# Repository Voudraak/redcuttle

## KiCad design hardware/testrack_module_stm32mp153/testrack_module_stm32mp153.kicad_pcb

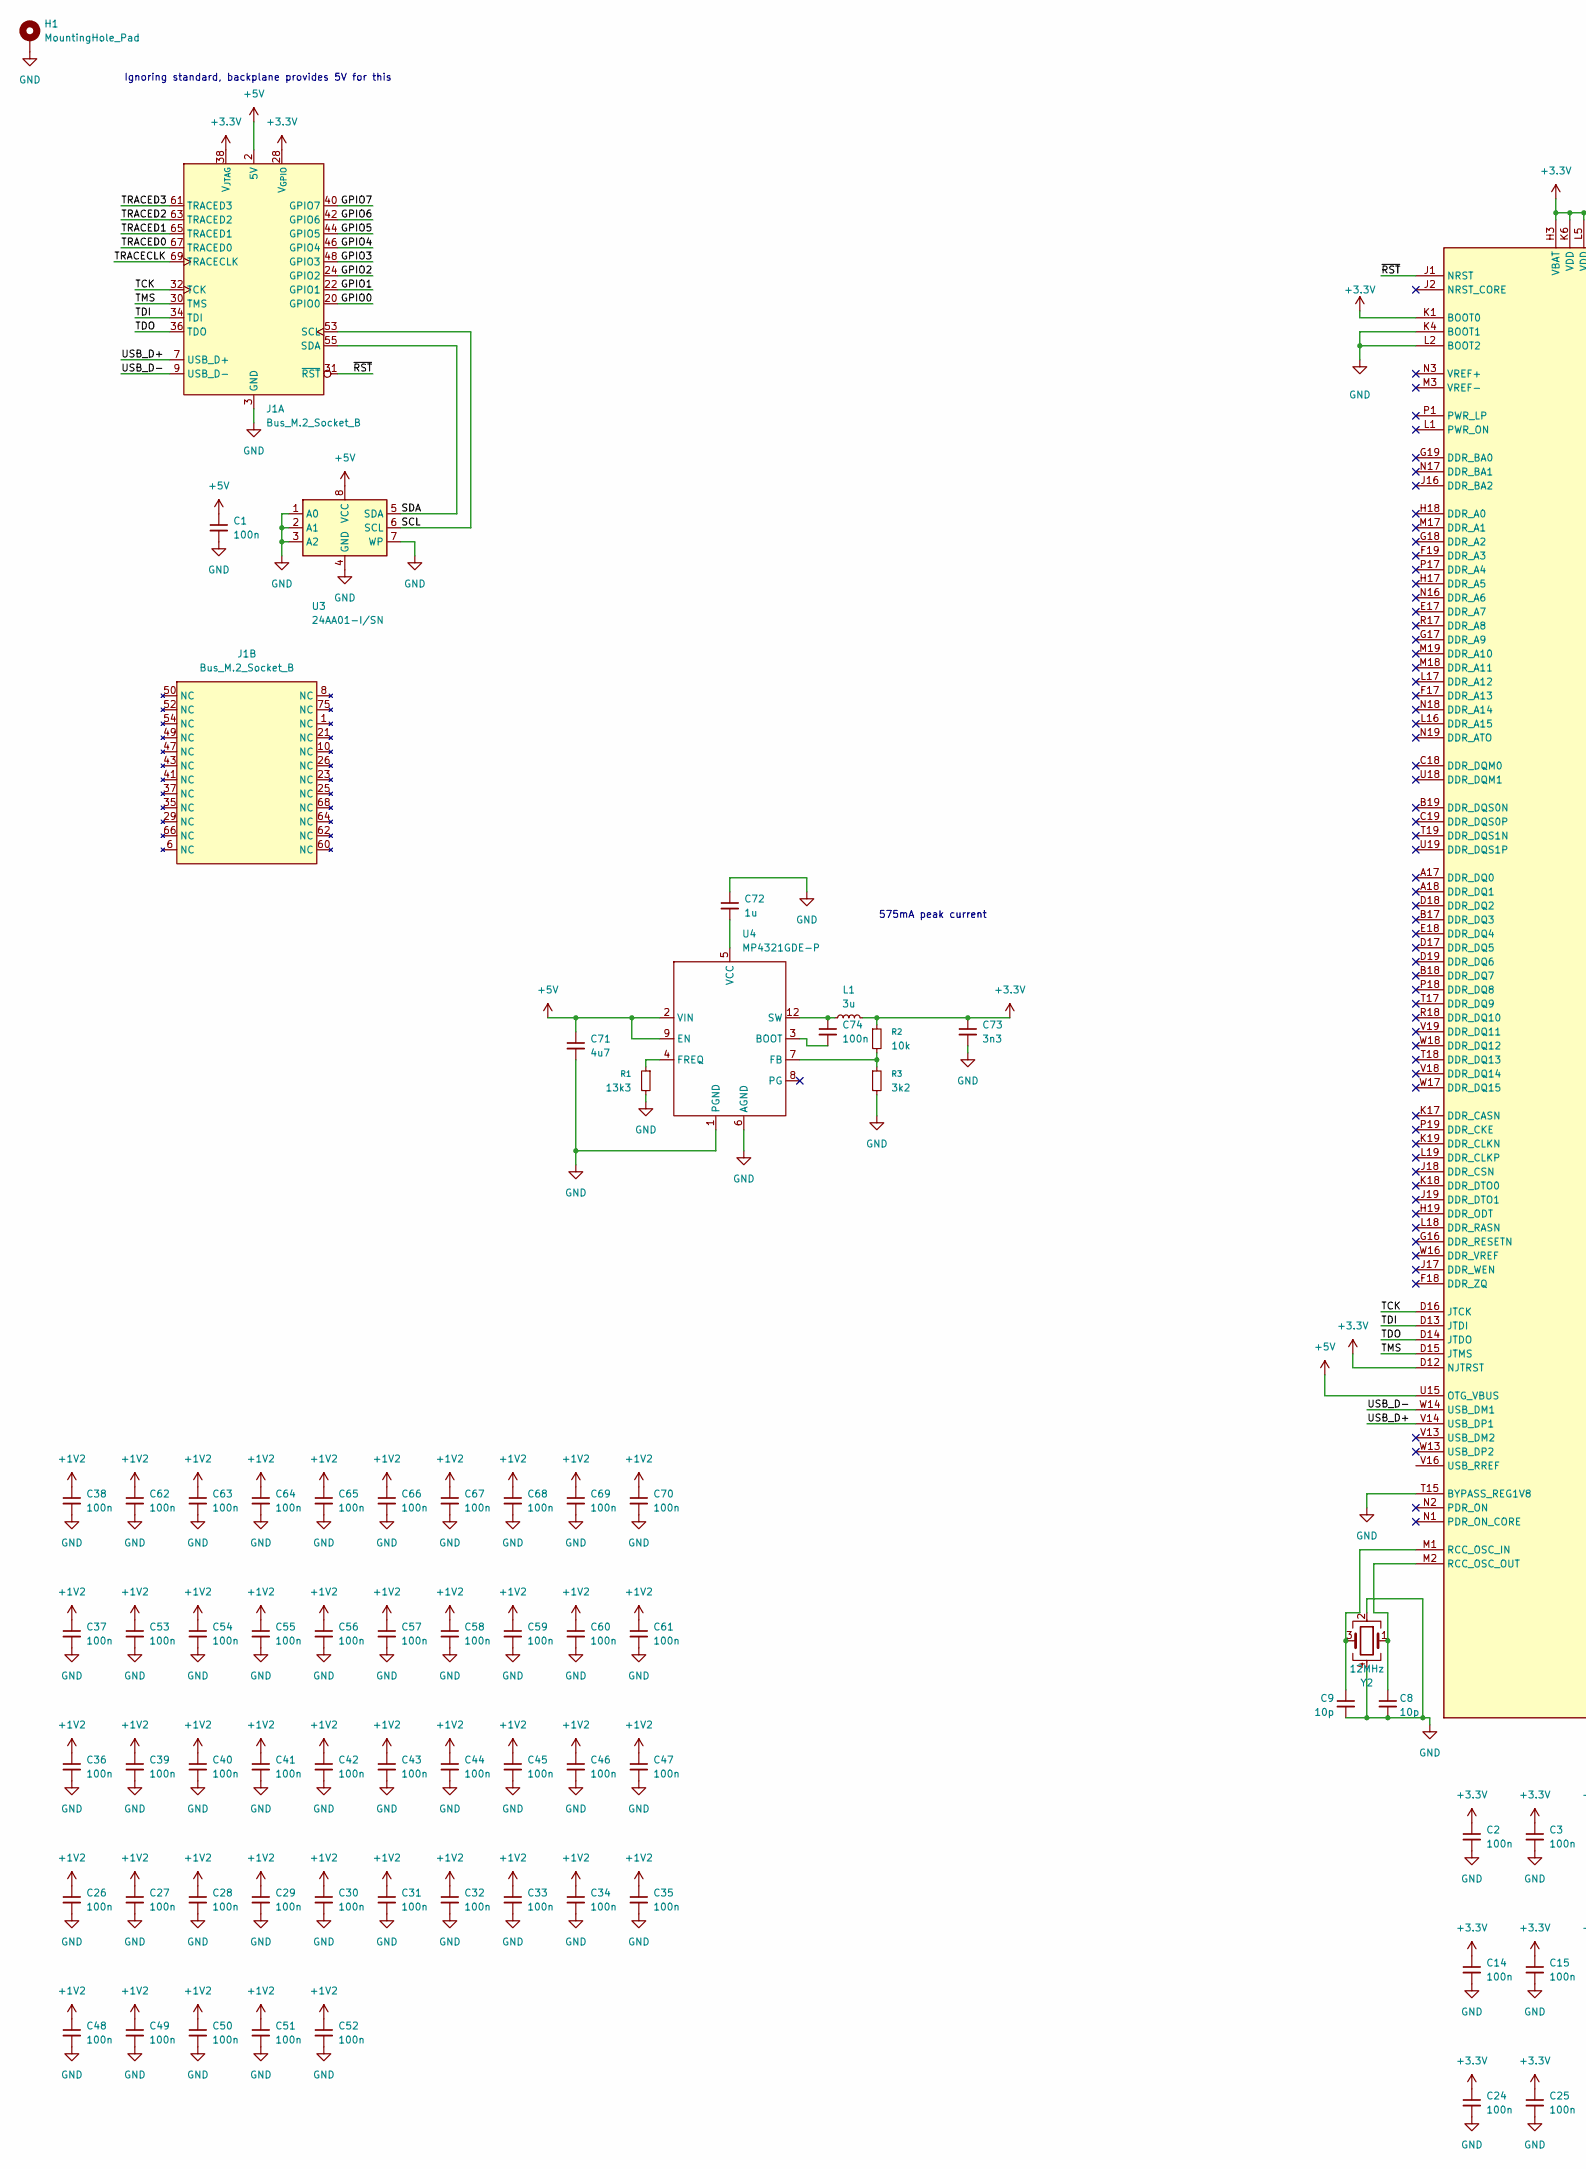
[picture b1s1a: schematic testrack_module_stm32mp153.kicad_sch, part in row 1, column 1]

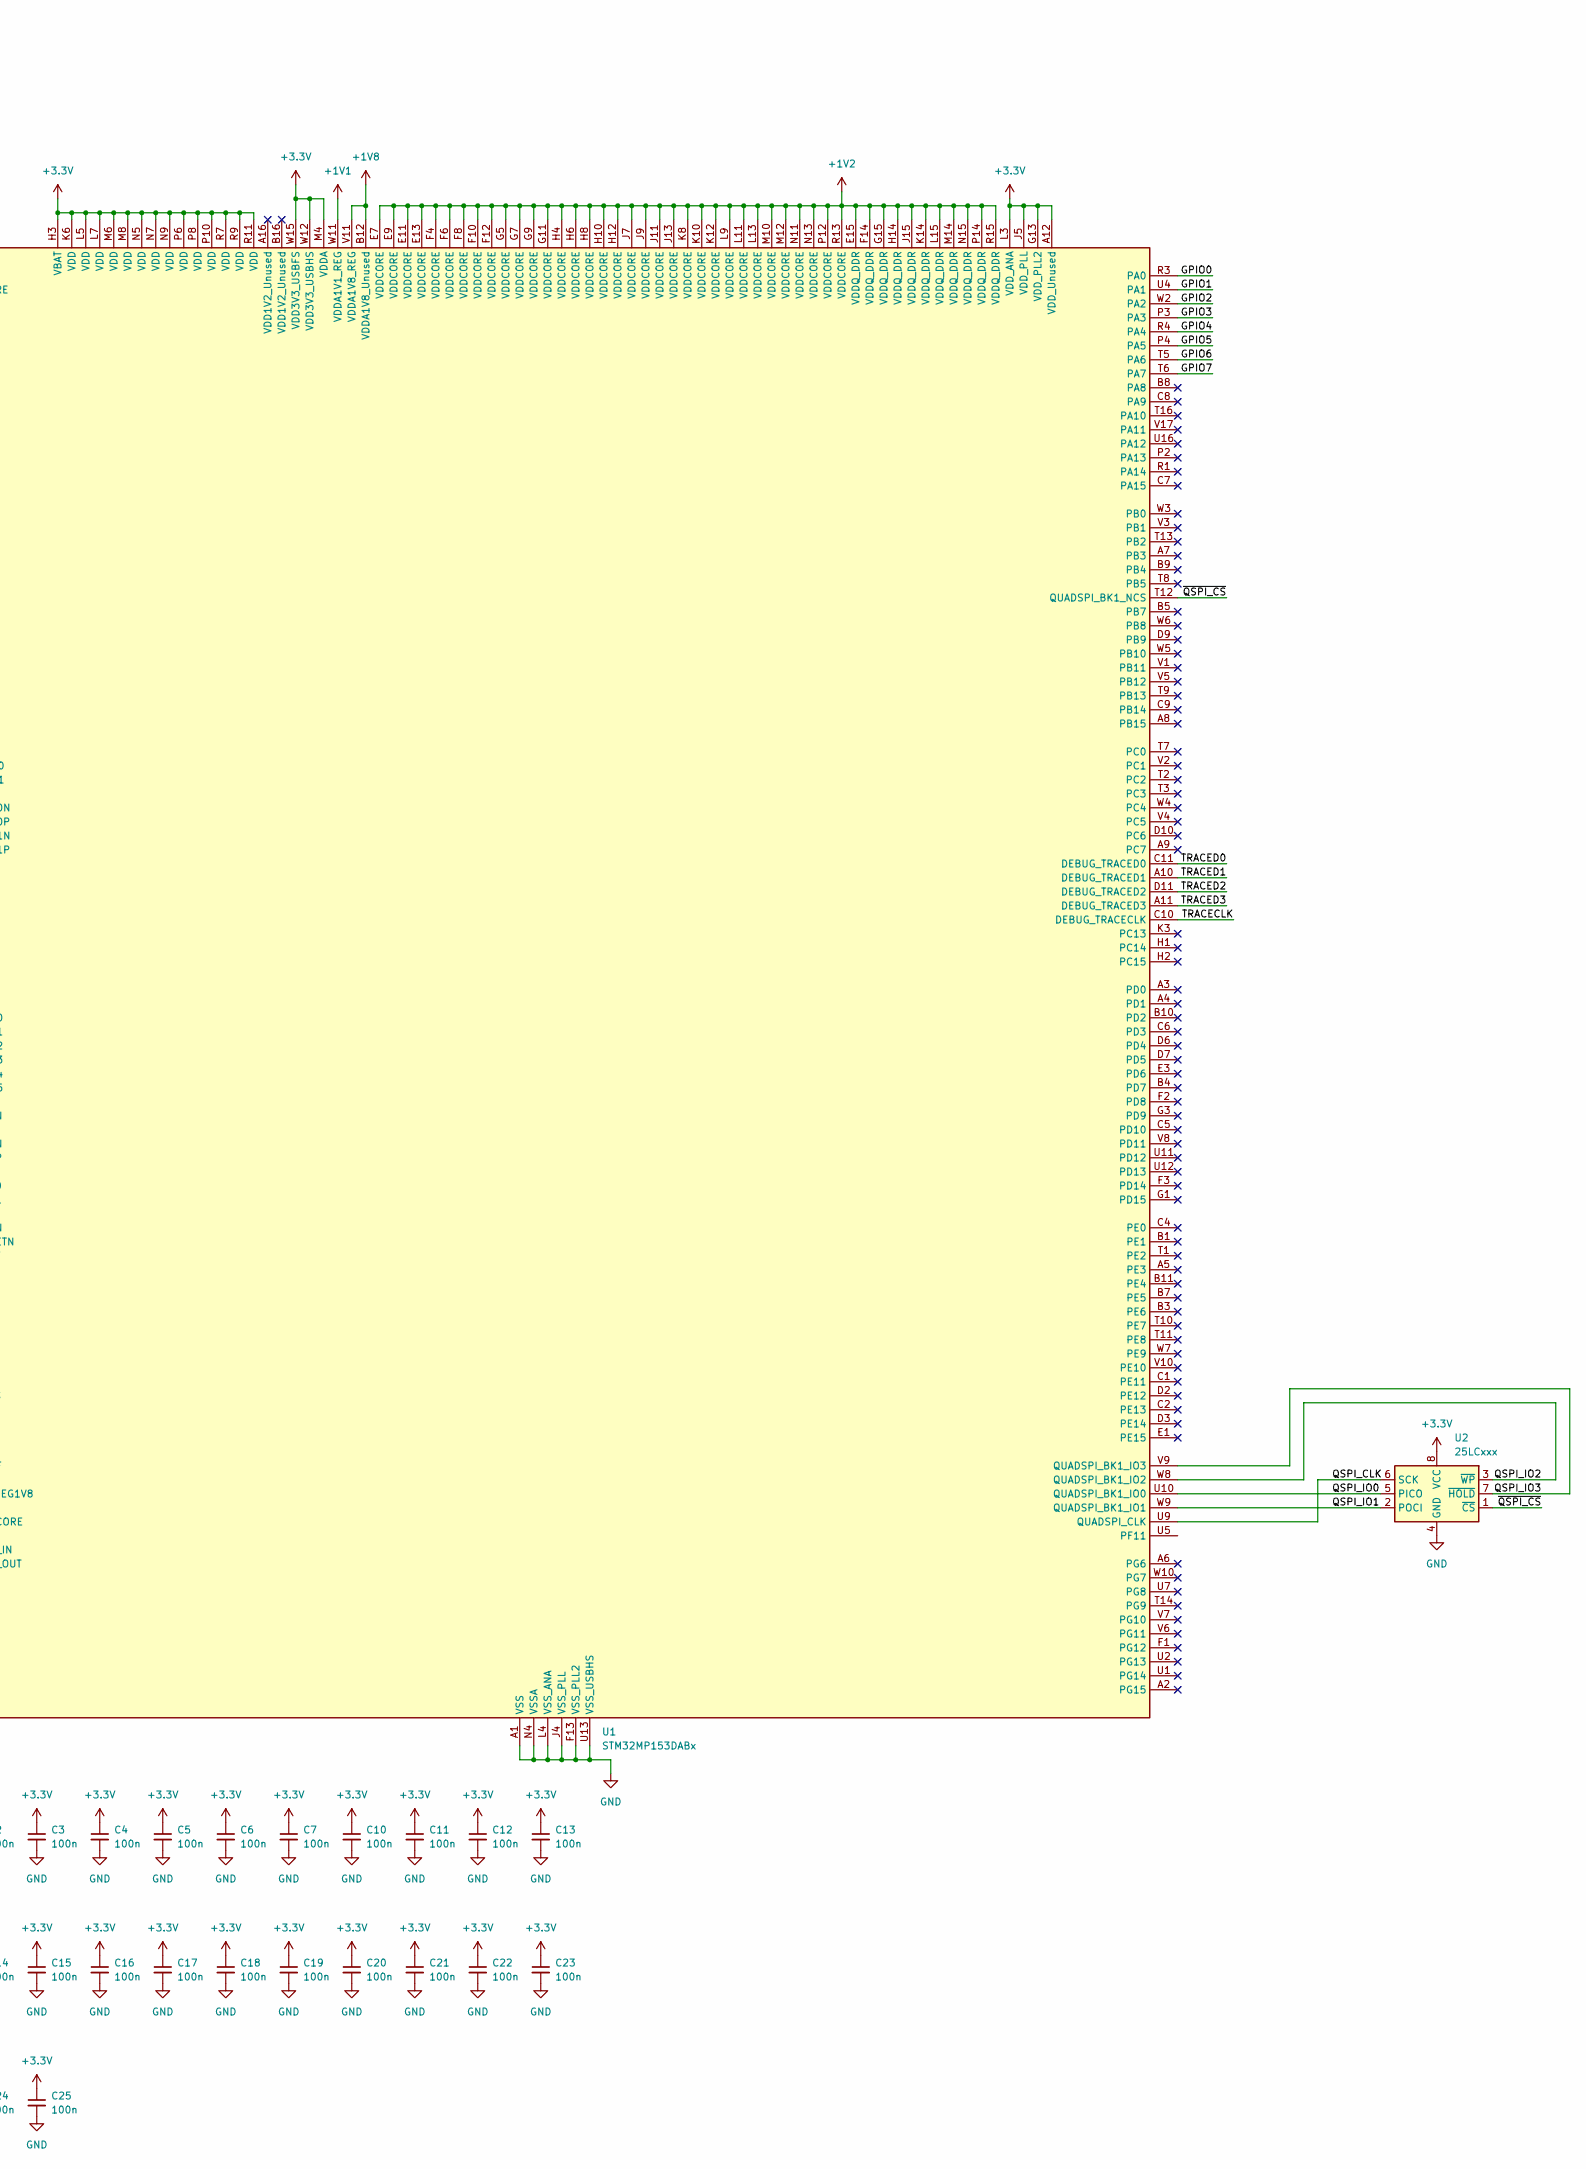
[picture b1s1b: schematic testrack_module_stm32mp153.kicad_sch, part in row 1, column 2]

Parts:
C1: 100n; C0603; MPN GRM188R71C104KA01J
C2, C3, C4, C5, C6, C7, C10, C11, C12, C13, C14, C15, C16, C17, C18, C19, C20, C21, C22, C23, C24, C25, C26, C27, C28, C29, C30, C31, C32, C33, C34, C35, C36, C37, C38, C39, C40, C41, C42, C43, C44, C45, C46, C47, C48, C49, C50, C51, C52, C53, C54, C55, C56, C57, C58, C59, C60, C61, C62, C63, C64, C65, C66, C67, C68, C69, C70: 100n; C0201; MPN GRM033R61A104KE84D
C8, C9: 10p; C0603; MPN CC0603JRNPO9BN100
C71: 4u7; C0603; MPN ZRB18AR6YA475KE05L
C72: 1u; C0603; MPN MC0603X105M160CT.
C73: 3n3; C0603; MPN MC0603N332F500CT
C74: 100n; C0603; MPN CC0603KRX7R8BB104
H1: MountingHole_Pad; MountingHole_2.7mm_M2.5_Pad
J1: Bus_M.2_Socket_B; NGFF_B
L1: 3u; IFSC2020
R1: 13k3; R0603; MPN MCWR06X1332FTL
R2: 10k; R0603; MPN MCWR06X1002FTL
R3: 3k2; R0603; MPN RN73H1JTTD3201F100
U1: STM32MP153DABx; ST_LFBGA-354_16x16mm_Layout19x19_P0.8mm; MPN STM32MP153DAB1
U2: 25LCxxx; UDFN-8-1EP_6x5mm_P1.27mm_EP3.4x4mm; MPN AT45DB161E-MHF-T
U3: 24AA01-I/SN; SO-8_3.9x4.9mm_P1.27mm; MPN 24AA01-I/SN
U4: MP4321GDE-P; QFN-12_2x3mm_P0.5mm; MPN MP4321GDE-P
Y2: 12MHz; SMD3225; MPN MCSJK-7U-12.00-12-10-80-B-10

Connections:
+1V1: U1.W11 (VDDA1V1_REG)
+1V2: C26.1, C27.1, C28.1, C29.1, C30.1, C31.1, C32.1, C33.1, C34.1, C35.1, C36.1, C37.1, C38.1, C39.1, C40.1, C41.1, C42.1, C43.1, C44.1, C45.1, C46.1, C47.1, C48.1, C49.1, C50.1, C51.1, C52.1, C53.1, C54.1, C55.1, C56.1, C57.1, C58.1, C59.1, C60.1, C61.1, C62.1, C63.1, C64.1, C65.1, C66.1, C67.1, C68.1, C69.1, C70.1, U1.E7 (VDDCORE), U1.E9 (VDDCORE), U1.E11 (VDDCORE), U1.E13 (VDDCORE), U1.E15 (VDDQ_DDR), U1.F4 (VDDCORE), U1.F6 (VDDCORE), U1.F8 (VDDCORE), U1.F10 (VDDCORE), U1.F12 (VDDCORE), U1.F14 (VDDQ_DDR), U1.G5 (VDDCORE), U1.G7 (VDDCORE), U1.G9 (VDDCORE), U1.G11 (VDDCORE), U1.G15 (VDDQ_DDR), U1.H4 (VDDCORE), U1.H6 (VDDCORE), U1.H8 (VDDCORE), U1.H10 (VDDCORE), U1.H12 (VDDCORE), U1.H14 (VDDQ_DDR), U1.J7 (VDDCORE), U1.J9 (VDDCORE), U1.J11 (VDDCORE), U1.J13 (VDDCORE), U1.J15 (VDDQ_DDR), U1.K8 (VDDCORE), U1.K10 (VDDCORE), U1.K12 (VDDCORE), U1.K14 (VDDQ_DDR), U1.L9 (VDDCORE), U1.L11 (VDDCORE), U1.L13 (VDDCORE), U1.L15 (VDDQ_DDR), U1.M10 (VDDCORE), U1.M12 (VDDCORE), U1.M14 (VDDQ_DDR), U1.N11 (VDDCORE), U1.N13 (VDDCORE), U1.N15 (VDDQ_DDR), U1.P12 (VDDCORE), U1.P14 (VDDQ_DDR), U1.R13 (VDDCORE), U1.R15 (VDDQ_DDR)
+1V8: U1.B12 (VDDA1V8_Unused), U1.V11 (VDDA1V8_REG)
+3.3V: C2.1, C3.1, C4.1, C5.1, C6.1, C7.1, C10.1, C11.1, C12.1, C13.1, C14.1, C15.1, C16.1, C17.1, C18.1, C19.1, C20.1, C21.1, C22.1, C23.1, C24.1, C25.1, C73.1, J1.28 (V_{GPIO}), J1.38 (V_{JTAG}), L1.2, R2.1, U1.A12 (VDD_Unused), U1.D12 (NJTRST), U1.G13 (VDD_PLL2), U1.H3 (VBAT), U1.J5 (VDD_PLL), U1.K1 (BOOT0), U1.K6 (VDD), U1.L3 (VDD_ANA), U1.L5 (VDD), U1.L7 (VDD), U1.M4 (VDDA), U1.M6 (VDD), U1.M8 (VDD), U1.N5 (VDD), U1.N7 (VDD), U1.N9 (VDD), U1.P6 (VDD), U1.P8 (VDD), U1.P10 (VDD), U1.R7 (VDD), U1.R9 (VDD), U1.R11 (VDD), U1.W12 (VDD3V3_USBHS), U1.W15 (VDD3V3_USBFS), U2.8 (VCC)
+5V: C1.1, C71.1, J1.2 (5V), J1.4 (5V), J1.70 (5V), J1.72 (5V), J1.74 (5V), U1.U15 (OTG_VBUS), U3.8 (VCC), U4.2 (VIN), U4.9 (EN), U4.10 (VIN)
/GPIO0: J1.20 (GPIO0), U1.R3 (PA0)
/GPIO1: J1.22 (GPIO1), U1.U4 (PA1)
/GPIO2: J1.24 (GPIO2), U1.W2 (PA2)
/GPIO3: J1.48 (GPIO3), U1.P3 (PA3)
/GPIO4: J1.46 (GPIO4), U1.R4 (PA4)
/GPIO5: J1.44 (GPIO5), U1.P4 (PA5)
/GPIO6: J1.42 (GPIO6), U1.T5 (PA6)
/GPIO7: J1.40 (GPIO7), U1.T6 (PA7)
/QSPI_CLK: U1.U9 (QUADSPI_CLK), U2.6 (SCK)
/QSPI_IO0: U1.U10 (QUADSPI_BK1_IO0), U2.5 (PICO)
/QSPI_IO1: U1.W9 (QUADSPI_BK1_IO1), U2.2 (POCI)
/QSPI_IO2: U1.W8 (QUADSPI_BK1_IO2), U2.3 (~WP)
/QSPI_IO3: U1.V9 (QUADSPI_BK1_IO3), U2.7 (~HOLD)
/SCL: J1.53 (SCL), U3.6 (SCL)
/SDA: J1.55 (SDA), U3.5 (SDA)
/TCK: J1.32 (TCK), U1.D16 (JTCK)
/TDI: J1.34 (TDI), U1.D13 (JTDI)
/TDO: J1.36 (TDO), U1.D14 (JTDO)
/TMS: J1.30 (TMS), U1.D15 (JTMS)
/TRACECLK: J1.69 (TRACECLK), U1.C10 (DEBUG_TRACECLK)
/TRACED0: J1.67 (TRACED0), U1.C11 (DEBUG_TRACED0)
/TRACED1: J1.65 (TRACED1), U1.A10 (DEBUG_TRACED1)
/TRACED2: J1.63 (TRACED2), U1.D11 (DEBUG_TRACED2)
/TRACED3: J1.61 (TRACED3), U1.A11 (DEBUG_TRACED3)
/USB_D+: J1.7 (USB_D+), U1.V14 (USB_DP1)
/USB_D-: J1.9 (USB_D-), U1.W14 (USB_DM1)
/~QSPI_CS: U1.T12 (QUADSPI_BK1_NCS), U2.1 (~CS)
/~RST: J1.31 (~RST), U1.J1 (NRST)
GND: C1.2, C2.2, C3.2, C4.2, C5.2, C6.2, C7.2, C8.2, C9.2, C10.2, C11.2, C12.2, C13.2, C14.2, C15.2, C16.2, C17.2, C18.2, C19.2, C20.2, C21.2, C22.2, C23.2, C24.2, C25.2, C26.2, C27.2, C28.2, C29.2, C30.2, C31.2, C32.2, C33.2, C34.2, C35.2, C36.2, C37.2, C38.2, C39.2, C40.2, C41.2, C42.2, C43.2, C44.2, C45.2, C46.2, C47.2, C48.2, C49.2, C50.2, C51.2, C52.2, C53.2, C54.2, C55.2, C56.2, C57.2, C58.2, C59.2, C60.2, C61.2, C62.2, C63.2, C64.2, C65.2, C66.2, C67.2, C68.2, C69.2, C70.2, C71.2, C72.1, C73.2, H1.1, J1.3 (GND), J1.5 (GND), J1.11 (GND), J1.27 (GND), J1.33 (GND), J1.39 (GND), J1.45 (GND), J1.51 (GND), J1.57 (GND), J1.71 (GND), J1.73 (GND), R1.2, R3.2, U1.A1 (VSS), U1.A19 (VSS), U1.B2 (VSS), U1.B6 (VSS), U1.C3 (VSS), U1.C12 (VSS), U1.C13 (VSS), U1.C14 (VSS), U1.C15 (VSS), U1.C16 (VSS), U1.C17 (VSS), U1.D1 (VSS), U1.D4 (VSS), U1.D5 (VSS), U1.D8 (VSS), U1.E2 (VSS), U1.E4 (VSS), U1.E5 (VSS), U1.E6 (VSS), U1.E8 (VSS), U1.E10 (VSS), U1.E12 (VSS), U1.E14 (VSS), U1.E16 (VSS), U1.F5 (VSS), U1.F7 (VSS), U1.F9 (VSS), U1.F11 (VSS), U1.F13 (VSS_PLL2), U1.F15 (VSS), U1.G2 (VSS), U1.G4 (VSS), U1.G6 (VSS), U1.G8 (VSS), U1.G10 (VSS), U1.G12 (VSS), U1.G14 (VSS), U1.H5 (VSS), U1.H7 (VSS), U1.H9 (VSS), U1.H11 (VSS), U1.H13 (VSS), U1.H15 (VSS), U1.J3 (VSS), U1.J4 (VSS_PLL), U1.J6 (VSS), U1.J8 (VSS), U1.J10 (VSS), U1.J12 (VSS), U1.J14 (VSS), U1.K2 (VSS), U1.K4 (BOOT1), U1.K5 (VSS), U1.K7 (VSS), U1.K9 (VSS), U1.K11 (VSS), U1.K13 (VSS), U1.K15 (VSS), U1.L2 (BOOT2), U1.L4 (VSS_ANA), U1.L6 (VSS), U1.L8 (VSS), U1.L10 (VSS), U1.L12 (VSS), U1.L14 (VSS), U1.M5 (VSS), U1.M7 (VSS), U1.M9 (VSS), U1.M11 (VSS), U1.M13 (VSS), U1.M15 (VSS), U1.N4 (VSSA), U1.N6 (VSS), U1.N8 (VSS), U1.N10 (VSS), U1.N12 (VSS), U1.N14 (VSS), U1.P5 (VSSA), U1.P7 (VSS), U1.P9 (VSS), U1.P11 (VSS), U1.P13 (VSS), U1.P15 (VSS), U1.R2 (VSS), U1.R5 (VSSA), U1.R6 (VSS), U1.R8 (VSS), U1.R10 (VSS), U1.R12 (VSS), U1.R14 (VSS), U1.R16 (VSS), U1.T4 (VSS), U1.T15 (BYPASS_REG1V8), U1.U3 (VSS), U1.U6 (VSS), U1.U8 (VSS), U1.U13 (VSS_USBHS), U1.U14 (VSS_USBHS), U1.U17 (VSS), U1.V12 (VSS_USBHS), U1.V15 (VSS_USBHS), U1.W1 (VSS), U1.W19 (VSS), U2.4 (GND), U2.9 (GND), U3.1 (A0), U3.2 (A1), U3.3 (A2), U3.4 (GND), U3.7 (WP), U4.1 (PGND), U4.6 (AGND), U4.11 (PGND), Y2.2, Y2.4
unnamed: C9.1, U1.M1 (RCC_OSC_IN), Y2.3
unnamed: C8.1, U1.M2 (RCC_OSC_OUT), Y2.1
unnamed: C74.2, U4.3 (BOOT)
unnamed: R2.2, R3.1, U4.7 (FB)
unnamed: R1.1, U4.4 (FREQ)
unnamed: C74.1, L1.1, U4.12 (SW)
unnamed: C72.2, U4.5 (VCC)

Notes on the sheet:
575mA peak current
Ignoring standard, backplane provides 5V for this

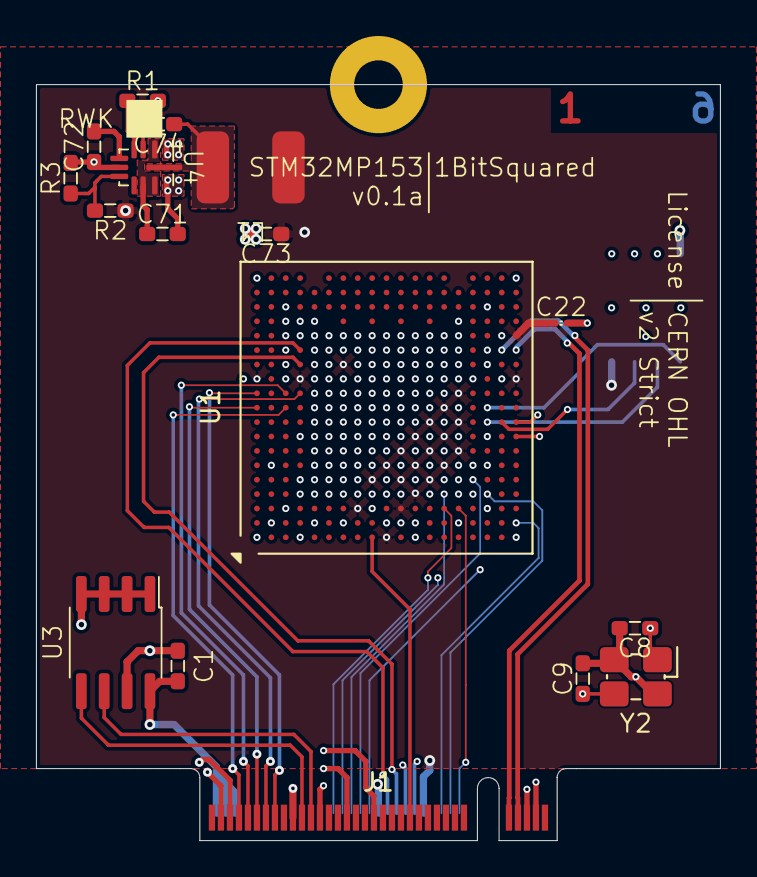
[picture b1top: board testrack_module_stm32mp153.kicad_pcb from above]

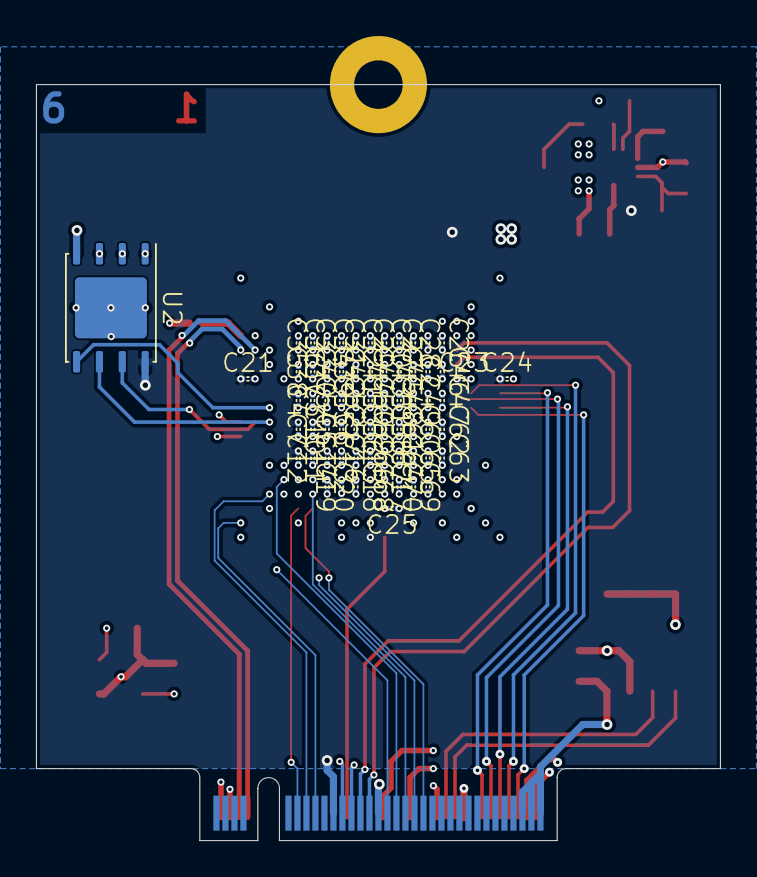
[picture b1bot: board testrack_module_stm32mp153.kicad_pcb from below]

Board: 6 copper layers, 38.0 x 42.0 mm, 85 parts (67 on the bottom side), 40 nets.

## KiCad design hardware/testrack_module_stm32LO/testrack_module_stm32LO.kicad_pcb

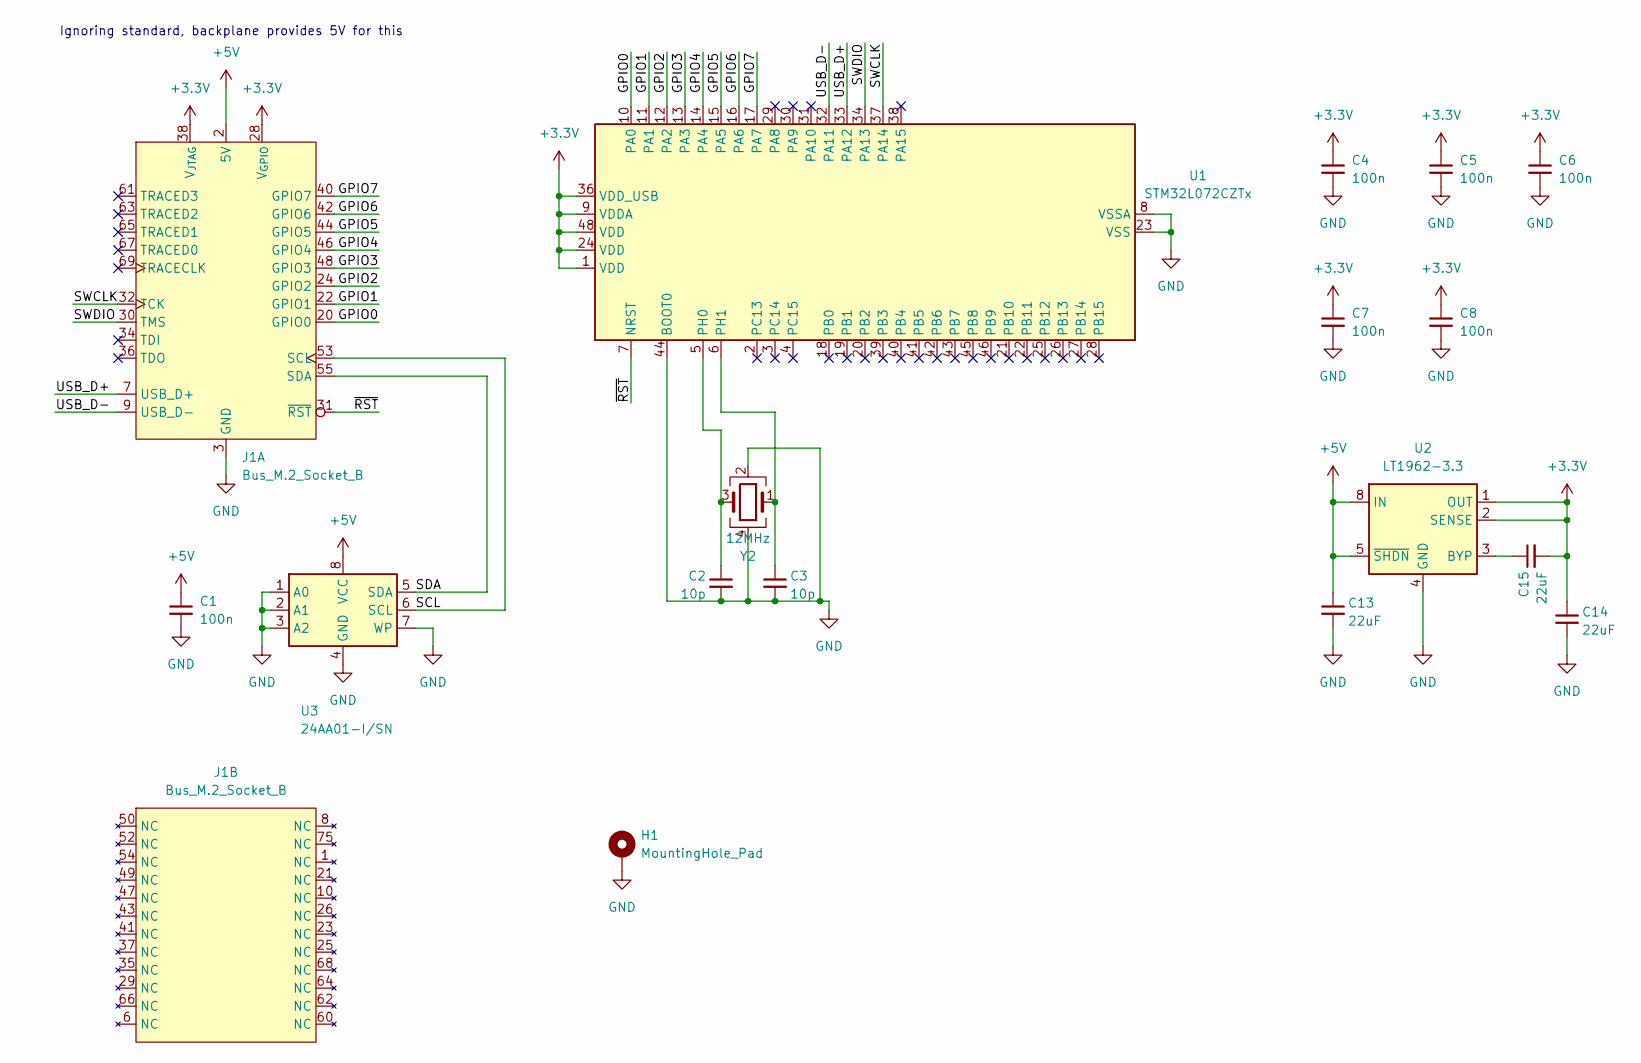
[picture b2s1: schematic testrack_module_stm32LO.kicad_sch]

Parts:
C1: 100n; C0603
C2, C3: 10p; C0603; MPN CC0603JRNPO9BN100
C4, C5, C6, C7, C8: 100n; C0603; MPN MC0603B104K100CT
C13, C14, C15: 22uF; C0603; MPN C1608X5R0J226M080AC
H1: MountingHole_Pad; MountingHole_2.7mm_M2.5_Pad
J1: Bus_M.2_Socket_B; NGFF_B
U1: STM32L072CZTx; LQFP-48_7x7mm_P0.5mm
U2: LT1962-3.3; MSOP-8_3x3mm_P0.65mm; MPN LT1962EMS8-3.3#TRPBF
U3: 24AA01-I/SN; SO-8_3.9x4.9mm_P1.27mm; MPN 24AA01-I/SN
Y2: 12MHz; SMD3225; MPN MCSJK-7U-12.00-12-10-80-B-10

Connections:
+3.3V: C4.1, C5.1, C6.1, C7.1, C8.1, C14.1, C15.2, J1.28 (V_{GPIO}), J1.38 (V_{JTAG}), U1.1 (VDD), U1.9 (VDDA), U1.24 (VDD), U1.36 (VDD_USB), U1.48 (VDD), U2.1 (OUT), U2.2 (SENSE)
+5V: C1.1, C13.1, J1.2 (5V), J1.4 (5V), J1.70 (5V), J1.72 (5V), J1.74 (5V), U2.5 (~SHDN), U2.8 (IN), U3.8 (VCC)
/GPIO0: J1.20 (GPIO0), U1.10 (PA0)
/GPIO1: J1.22 (GPIO1), U1.11 (PA1)
/GPIO2: J1.24 (GPIO2), U1.12 (PA2)
/GPIO3: J1.48 (GPIO3), U1.13 (PA3)
/GPIO4: J1.46 (GPIO4), U1.14 (PA4)
/GPIO5: J1.44 (GPIO5), U1.15 (PA5)
/GPIO6: J1.42 (GPIO6), U1.16 (PA6)
/GPIO7: J1.40 (GPIO7), U1.17 (PA7)
/SCL: J1.53 (SCL), U3.6 (SCL)
/SDA: J1.55 (SDA), U3.5 (SDA)
/SWCLK: J1.32 (TCK), U1.37 (PA14)
/SWDIO: J1.30 (TMS), U1.34 (PA13)
/USB_D+: J1.7 (USB_D+), U1.33 (PA12)
/USB_D-: J1.9 (USB_D-), U1.32 (PA11)
/~RST: J1.31 (~RST), U1.7 (NRST)
GND: C1.2, C2.2, C3.2, C4.2, C5.2, C6.2, C7.2, C8.2, C13.2, C14.2, H1.1, J1.3 (GND), J1.5 (GND), J1.11 (GND), J1.27 (GND), J1.33 (GND), J1.39 (GND), J1.45 (GND), J1.51 (GND), J1.57 (GND), J1.71 (GND), J1.73 (GND), U1.8 (VSSA), U1.23 (VSS), U1.35 (VSS), U1.44 (BOOT0), U1.47 (VSS), U2.4 (GND), U3.1 (A0), U3.2 (A1), U3.3 (A2), U3.4 (GND), U3.7 (WP), Y2.2, Y2.4
unnamed: C2.1, U1.5 (PH0), Y2.3
unnamed: C3.1, U1.6 (PH1), Y2.1
unnamed: C15.1, U2.3 (BYP)

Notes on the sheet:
Ignoring standard, backplane provides 5V for this

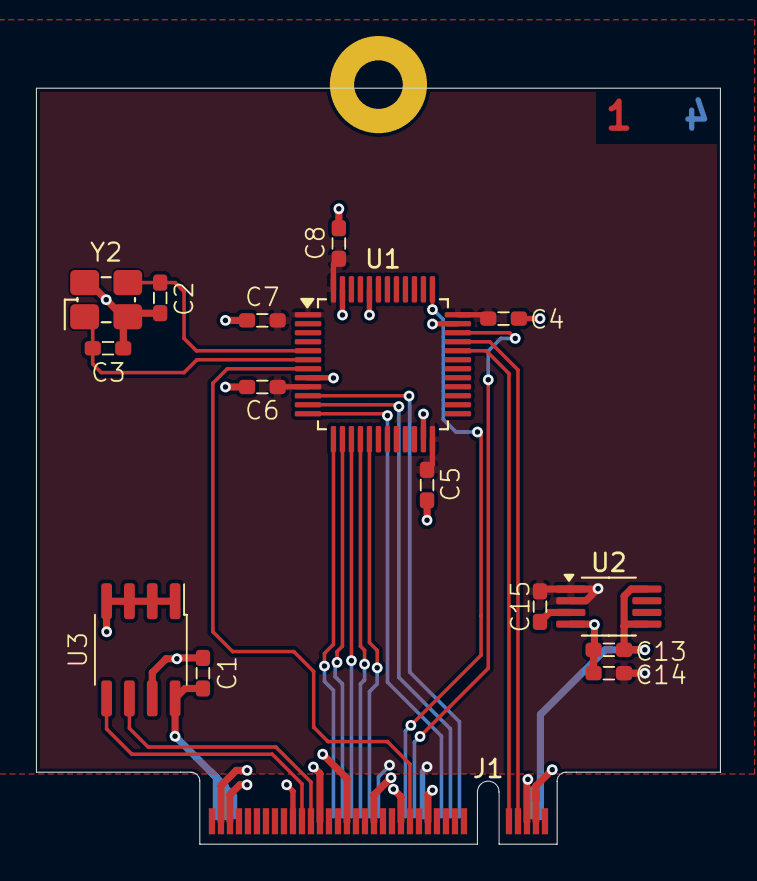
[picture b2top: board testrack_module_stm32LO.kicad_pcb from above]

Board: 4 copper layers, 38.0 x 42.0 mm, 17 parts (0 on the bottom side), 21 nets.

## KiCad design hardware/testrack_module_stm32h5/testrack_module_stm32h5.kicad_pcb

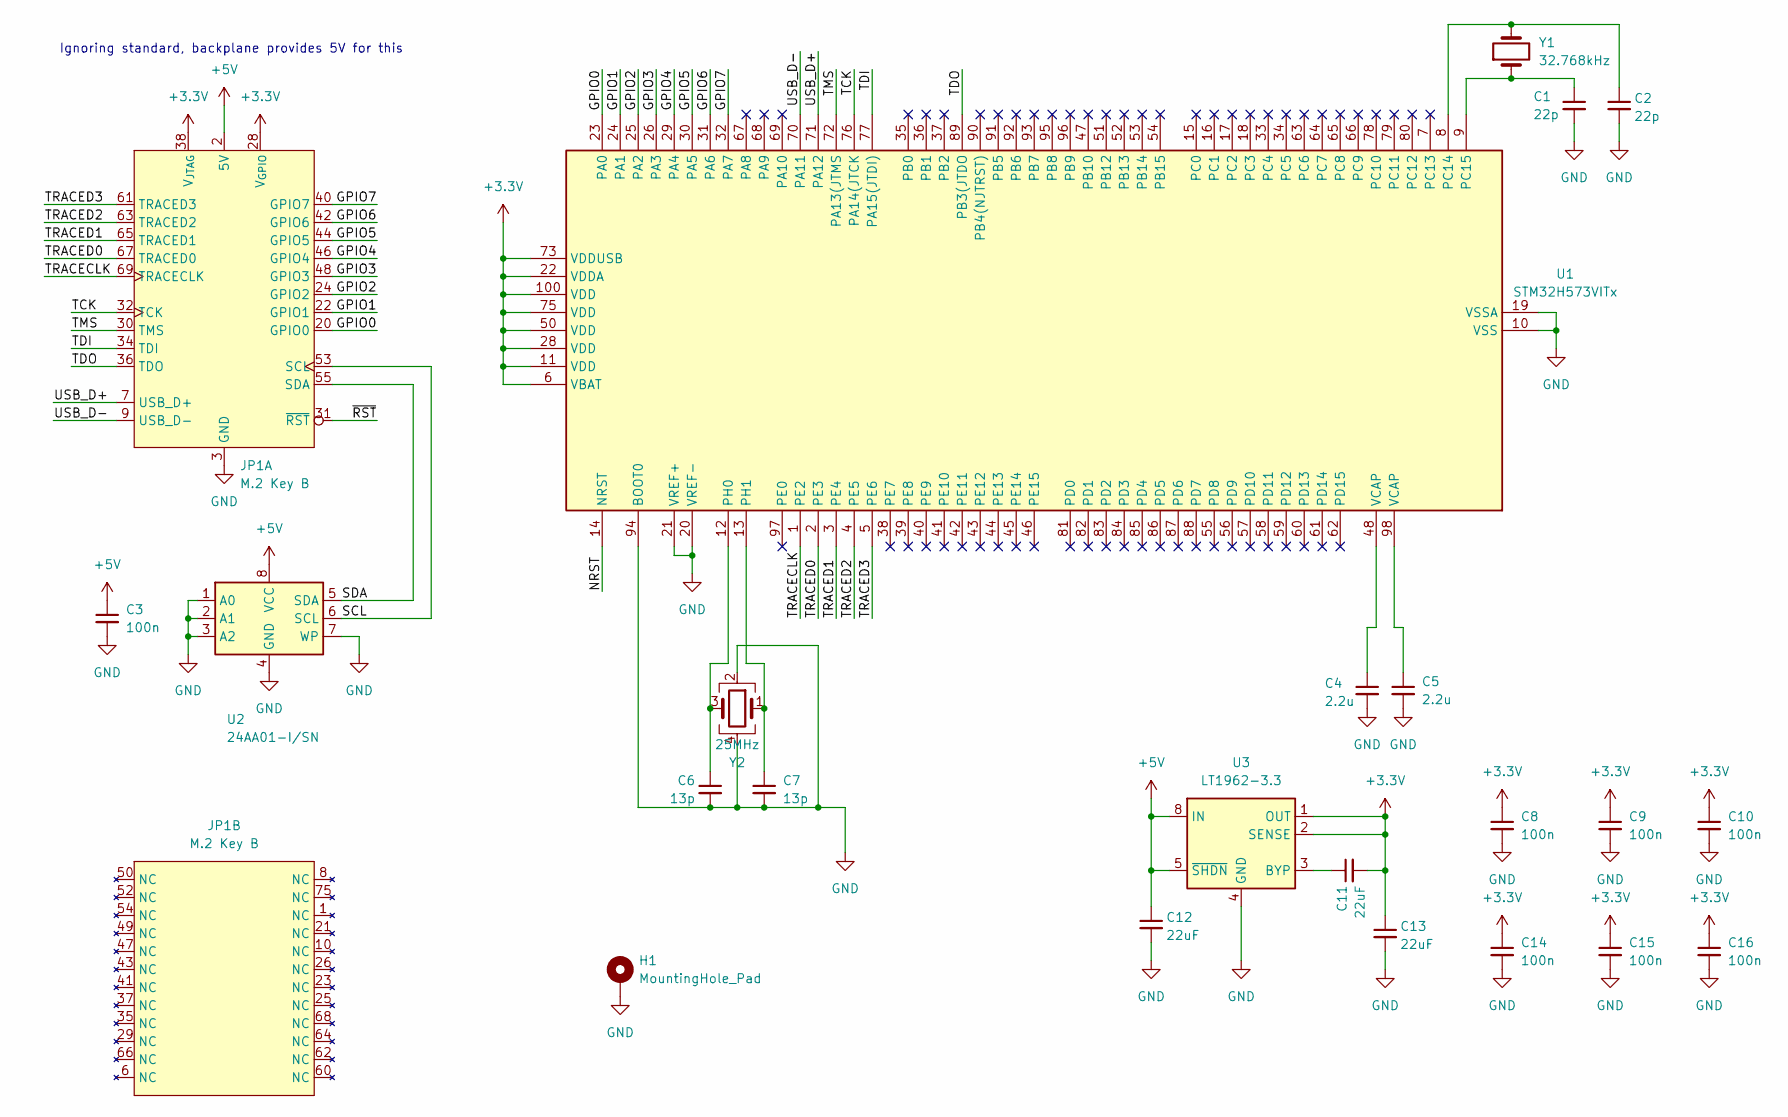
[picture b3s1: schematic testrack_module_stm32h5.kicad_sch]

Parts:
C1, C2: 22p; C0603; MPN C0603C0G1H220J030BA
C3: 100n; C0603
C4, C5: 2.2u; C0603; MPN MC0603X225K100CT
C6, C7: 13p; C0603
C8, C9, C10, C14, C15, C16: 100n; C0603; MPN MC0603B104K100CT
C11, C12, C13: 22uF; C0603; MPN C1608X5R0J226M080AC
H1: MountingHole_Pad; MountingHole_2.7mm_M2.5_Pad
JP1: M.2 Key B; NGFF_B
U1: STM32H573VITx; LQFP-100_14x14mm_P0.5mm
U2: 24AA01-I/SN; SO-8_3.9x4.9mm_P1.27mm; MPN 24AA01-I/SN
U3: LT1962-3.3; MSOP-8_3x3mm_P0.65mm; MPN LT1962EMS8-3.3#TRPBF
Y1: 32.768kHz; SMD3215; MPN MPJK-7L-32.768-12.5-20-70-C
Y2: 25MHz; SMD3225; MPN MCSJK-7U-12.00-12-10-80-B-10

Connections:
+3.3V: C8.1, C9.1, C10.1, C11.2, C13.1, C14.1, C15.1, C16.1, JP1.28 (V_{GPIO}), JP1.38 (V_{JTAG}), U1.6 (VBAT), U1.11 (VDD), U1.22 (VDDA), U1.28 (VDD), U1.50 (VDD), U1.73 (VDDUSB), U1.75 (VDD), U1.100 (VDD), U3.1 (OUT), U3.2 (SENSE)
+5V: C3.1, C12.1, JP1.2 (5V), JP1.4 (5V), JP1.70 (5V), JP1.72 (5V), JP1.74 (5V), U2.8 (VCC), U3.5 (~SHDN), U3.8 (IN)
/GPIO0: JP1.20 (GPIO0), U1.23 (PA0)
/GPIO1: JP1.22 (GPIO1), U1.24 (PA1)
/GPIO2: JP1.24 (GPIO2), U1.25 (PA2)
/GPIO3: JP1.48 (GPIO3), U1.26 (PA3)
/GPIO4: JP1.46 (GPIO4), U1.29 (PA4)
/GPIO5: JP1.44 (GPIO5), U1.30 (PA5)
/GPIO6: JP1.42 (GPIO6), U1.31 (PA6)
/GPIO7: JP1.40 (GPIO7), U1.32 (PA7)
/NRST: U1.14 (NRST)
/SCL: JP1.53 (SCL), U2.6 (SCL)
/SDA: JP1.55 (SDA), U2.5 (SDA)
/TCK: JP1.32 (TCK), U1.76 (PA14(JTCK)
/TDI: JP1.34 (TDI), U1.77 (PA15(JTDI))
/TDO: JP1.36 (TDO), U1.89 (PB3(JTDO)
/TMS: JP1.30 (TMS), U1.72 (PA13(JTMS)
/TRACECLK: JP1.69 (TRACECLK), U1.1 (PE2)
/TRACED0: JP1.67 (TRACED0), U1.2 (PE3)
/TRACED1: JP1.65 (TRACED1), U1.3 (PE4)
/TRACED2: JP1.63 (TRACED2), U1.4 (PE5)
/TRACED3: JP1.61 (TRACED3), U1.5 (PE6)
/USB_D+: JP1.7 (USB_D+), U1.71 (PA12)
/USB_D-: JP1.9 (USB_D-), U1.70 (PA11)
/~RST: JP1.31 (~RST)
GND: C1.2, C2.2, C3.2, C4.2, C5.2, C6.2, C7.2, C8.2, C9.2, C10.2, C12.2, C13.2, C14.2, C15.2, C16.2, H1.1, JP1.3 (GND), JP1.5 (GND), JP1.11 (GND), JP1.27 (GND), JP1.33 (GND), JP1.39 (GND), JP1.45 (GND), JP1.51 (GND), JP1.57 (GND), JP1.71 (GND), JP1.73 (GND), U1.10 (VSS), U1.19 (VSSA), U1.20 (VREF-), U1.21 (VREF+), U1.27 (VSS), U1.49 (VSS), U1.74 (VSS), U1.94 (BOOT0), U1.99 (VSS), U2.1 (A0), U2.2 (A1), U2.3 (A2), U2.4 (GND), U2.7 (WP), U3.4 (GND), Y2.2, Y2.4
unnamed: C4.1, U1.48 (VCAP)
unnamed: C5.1, U1.98 (VCAP)
unnamed: C2.1, U1.8 (PC14), Y1.2
unnamed: C1.1, U1.9 (PC15), Y1.1
unnamed: C6.1, U1.12 (PH0), Y2.3
unnamed: C7.1, U1.13 (PH1), Y2.1
unnamed: C11.1, U3.3 (BYP)

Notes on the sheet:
Ignoring standard, backplane provides 5V for this

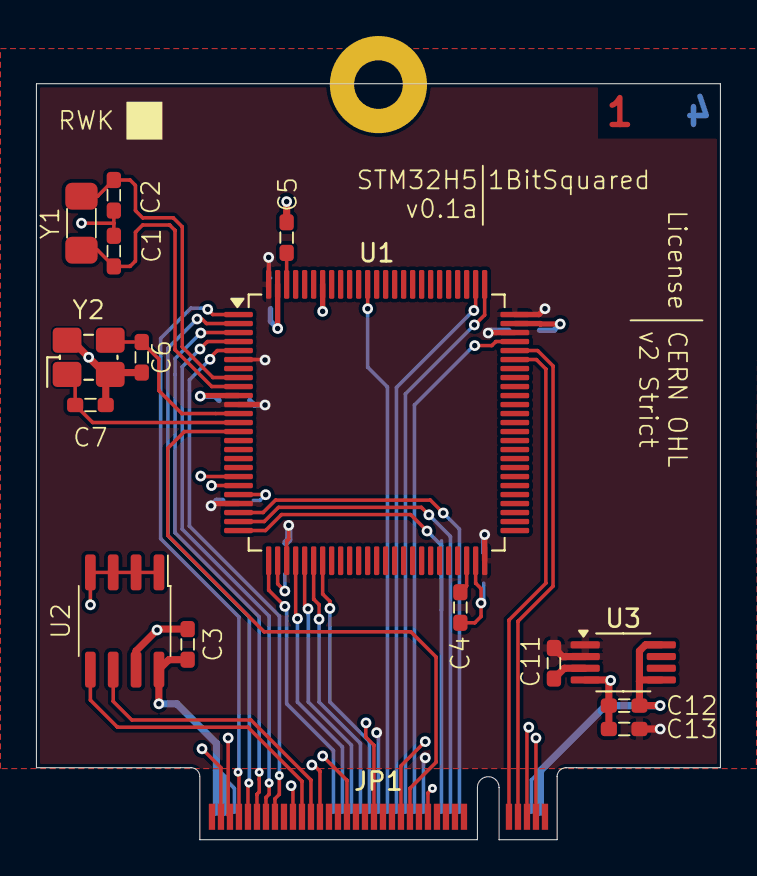
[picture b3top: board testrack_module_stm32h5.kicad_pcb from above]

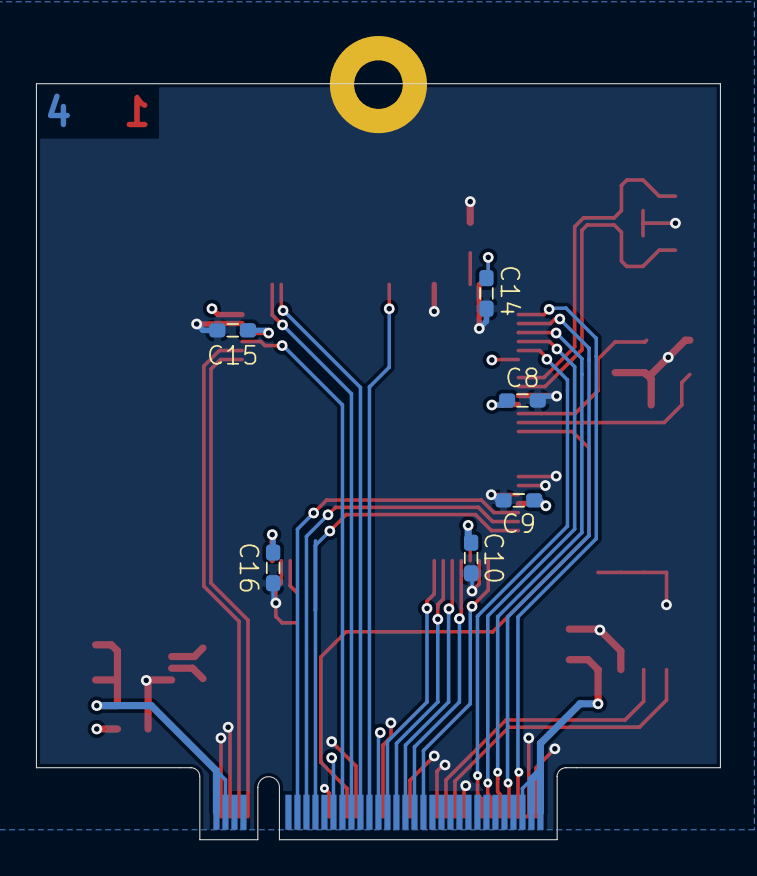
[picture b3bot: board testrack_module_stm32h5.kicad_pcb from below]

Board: 4 copper layers, 38.0 x 42.0 mm, 23 parts (6 on the bottom side), 31 nets.

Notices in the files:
hardware/testrack_breakout/testrack_breakout.kicad_pcb:
CERN OHL
